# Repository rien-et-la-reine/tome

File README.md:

# tome

seeing if i can make a clamshell ereader + music player from scratch(-ish)

inspired in part by The Open Book (https://github.com/joeycastillo/The-Open-Book)

Firmware: [tavernkeep](https://github.com/rien-et-la-reine/tavernkeep)

## License

Copyright Harsh Patel 2026.

The following notice applies to all hardware design files in this repository.

This source describes Open Hardware and is licensed under the CERN-OHL-S v2.
You may redistribute and modify this source and make products using it under the terms of the CERN-OHL-S v2 (https://ohwr.org/cern_ohl_s_v2.txt).

This source is distributed WITHOUT ANY EXPRESS OR IMPLIED WARRANTY, INCLUDING OF MERCHANTABILITY, SATISFACTORY QUALITY AND FITNESS FOR A PARTICULAR PURPOSE.
Please see the CERN-OHL-S v2 for applicable conditions.

Source location: https://github.com/rien-et-la-reine/tome

As per CERN-OHL-S v2 section 4, should you produce hardware based on this source, you must where practicable maintain the Source Location visible on the external case or other products you make using this source.

Commits up to and including `8ce5c31` were published under CC BY-SA 4.0 and remain available under that licence.

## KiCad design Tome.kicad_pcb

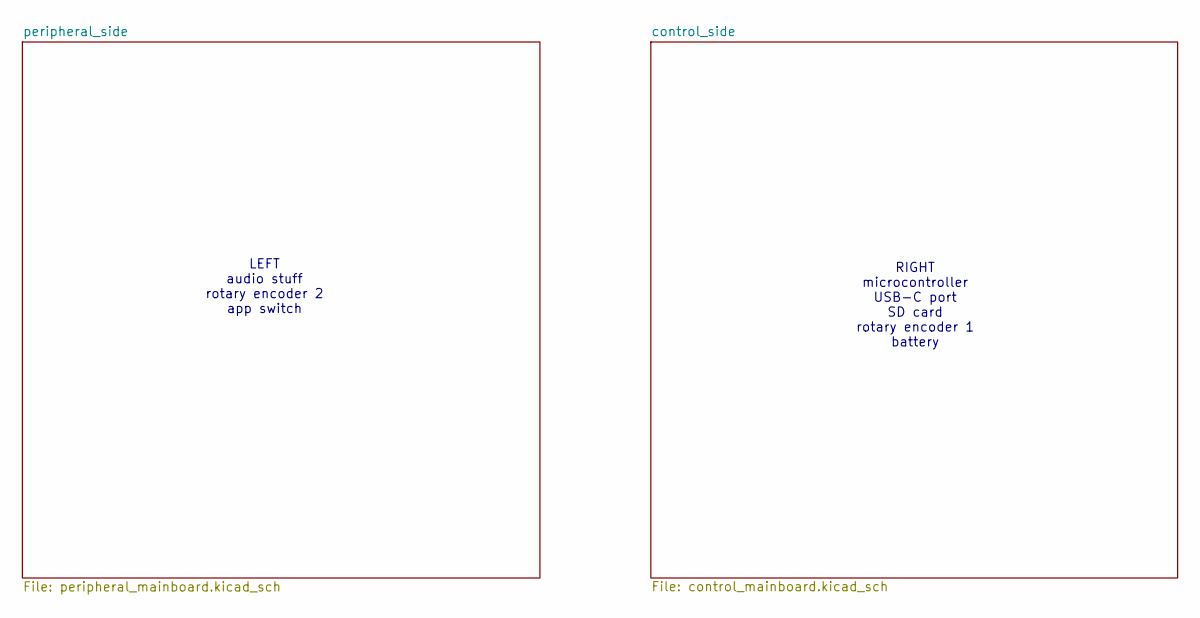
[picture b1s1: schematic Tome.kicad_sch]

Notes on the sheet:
RIGHT microcontroller USB-C port SD card rotary encoder 1 battery
LEFT audio stuff rotary encoder 2 app switch

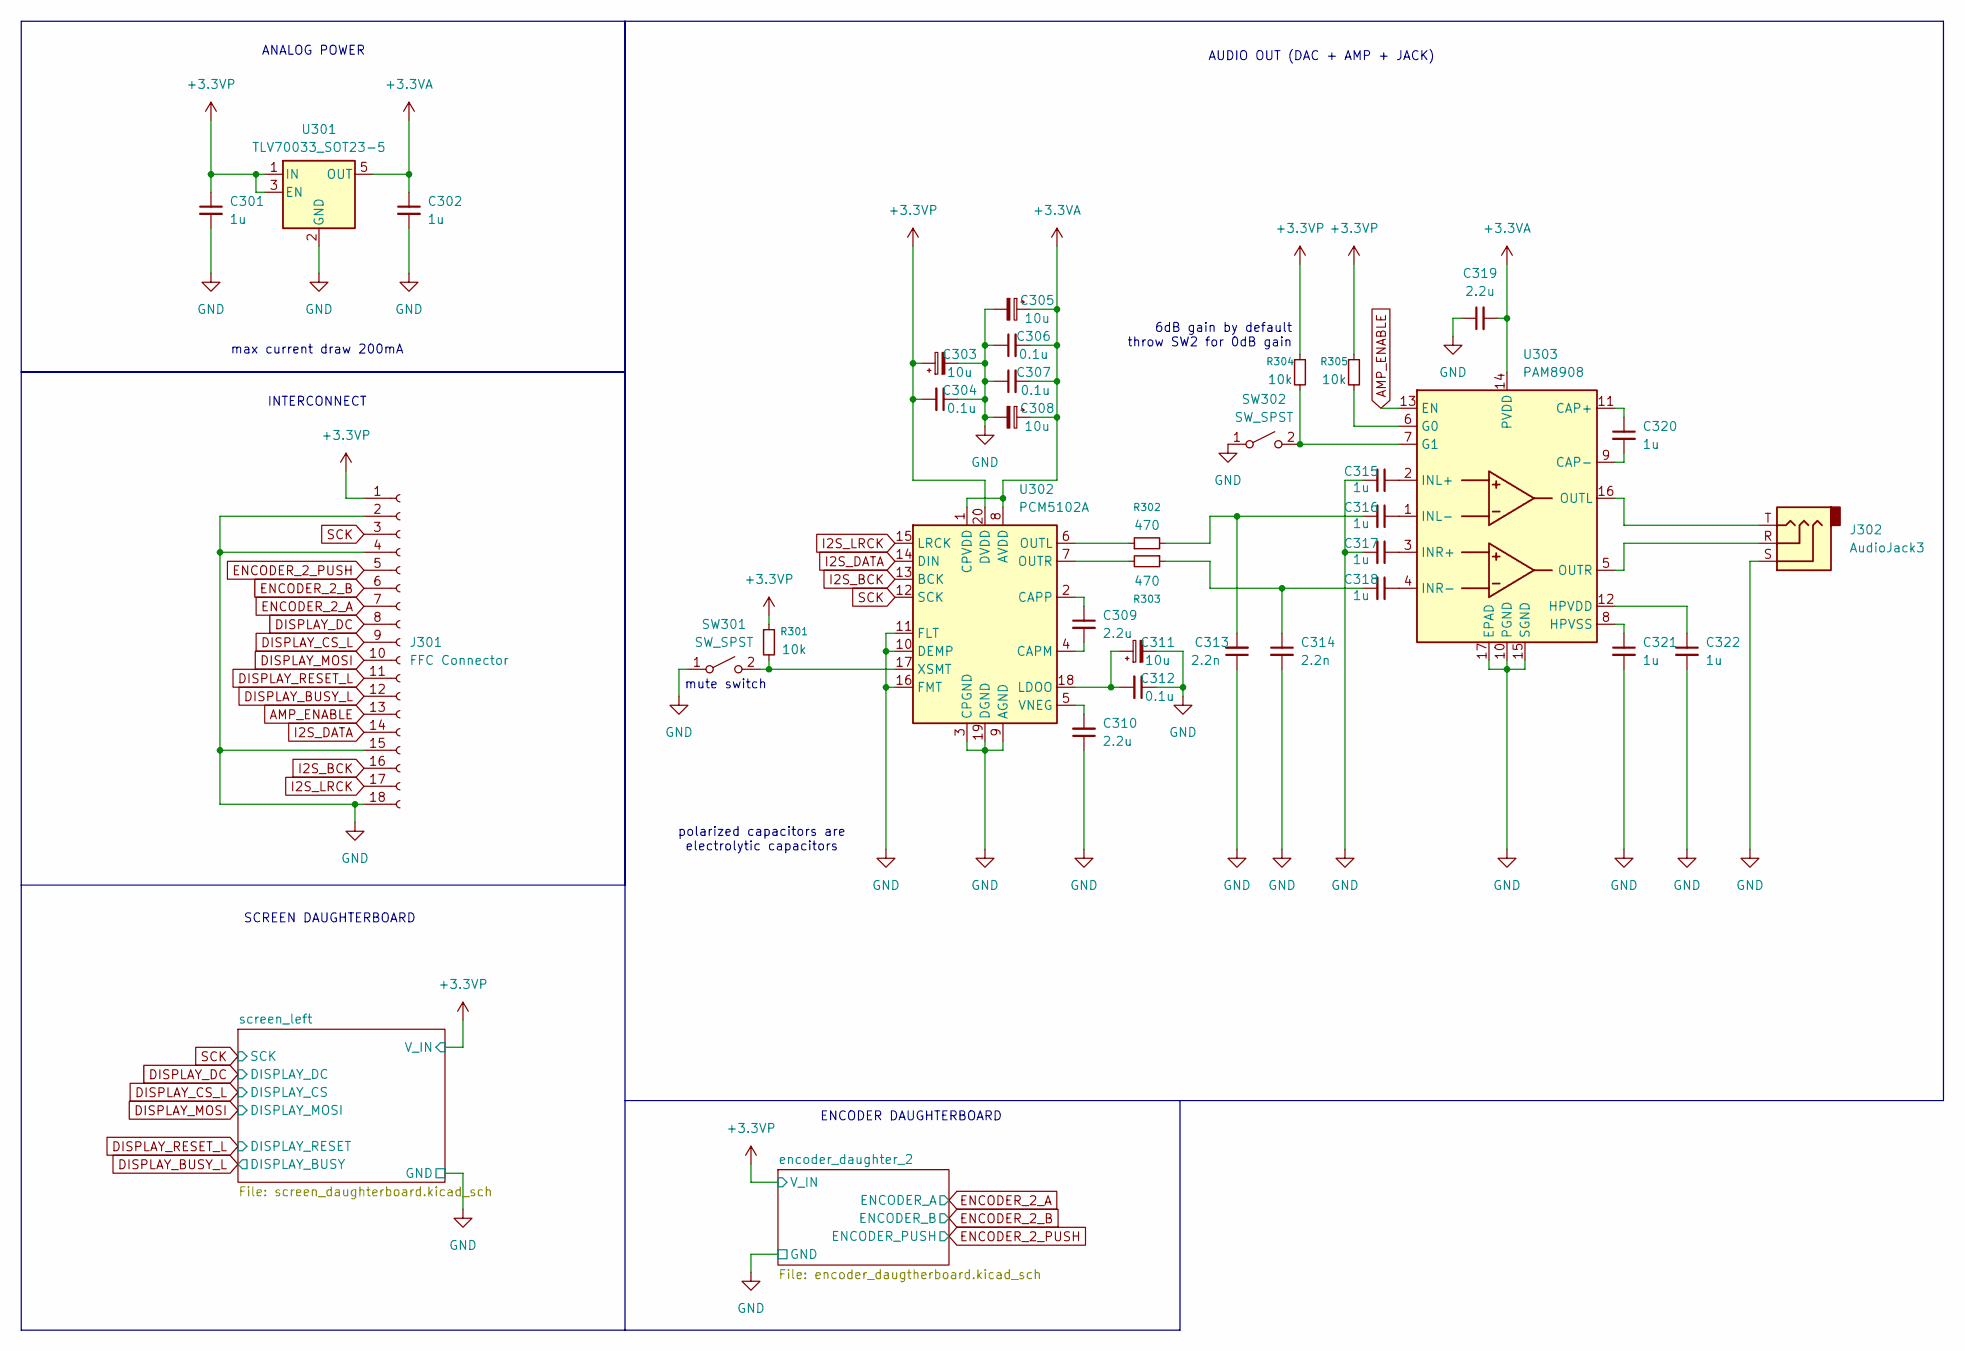
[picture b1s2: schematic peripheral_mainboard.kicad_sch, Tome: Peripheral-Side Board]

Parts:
C301, C302, C315, C316, C317, C318, C320, C321, C322: 1u; C_0805_2012Metric
C303, C305, C308, C311: 10u; CP_Elec_4x4.5
C304, C306, C307, C312: 0.1u; C_1206_3216Metric
C309, C310, C319: 2.2u; C_0402_1005Metric
C313, C314: 2.2n; C_0805_2012Metric
J301: FFC Connector; JUSHUO_AFA07-S18FCA-00_1x18-1MP_P1.0mm_Horizontal
J302: AudioJack3; Jack_3.5mm_CUI_SJ1-3523N_Horizontal
R301, R304, R305: 10k; R_1206_3216Metric
R302, R303: 470; R_0603_1608Metric
SW301, SW302: SW_SPST; SW_SPDT_CK_JS102011SAQN
U301: TLV70033_SOT23-5; SOT-23-5
U302: PCM5102A; TSSOP-20_4.4x6.5mm_P0.65mm
U303: PAM8908; QFN-16-1EP_3x3mm_P0.5mm_EP1.7x1.7mm

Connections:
+3.3VA: C302.1, C305.1, C306.2, C307.2, C308.1, C319.2, U301.5 (OUT), U302.1 (CPVDD), U302.8 (AVDD), U303.14 (PVDD)
+3.3VP: C301.1, C303.1, C304.2, J301.1, R301.1, R304.1, R305.1, U301.1 (IN), U301.3 (EN), U302.20 (DVDD); also elsewhere on the board
AMP_ENABLE: J301.13, U303.13 (EN); also elsewhere on the board
DISPLAY_BUSY_L: J301.12; also elsewhere on the board
DISPLAY_CS_L: J301.9; also elsewhere on the board
DISPLAY_DC: J301.8; also elsewhere on the board
DISPLAY_MOSI: J301.10; also elsewhere on the board
DISPLAY_RESET_L: J301.11; also elsewhere on the board
ENCODER_2_A: J301.7; also elsewhere on the board
ENCODER_2_B: J301.6; also elsewhere on the board
ENCODER_2_PUSH: J301.5; also elsewhere on the board
GND: C301.2, C302.2, C303.2, C304.1, C305.2, C306.1, C307.1, C308.2, C310.1, C311.2, C312.1, C313.1, C314.2, C315.2, C317.2, C319.1, C321.2, C322.2, J301.2, J301.4, J301.15, J301.18, J302.S, SW301.1 (A), SW302.1 (A), U301.2 (GND), U302.3 (CPGND), U302.9 (AGND), U302.10 (DEMP), U302.11 (FLT), U302.16 (FMT), U302.19 (DGND), U303.10 (PGND), U303.15 (SGND), U303.17 (EPAD); also elsewhere on the board
I2S_BCK: J301.16, U302.13 (BCK); also elsewhere on the board
I2S_DATA: J301.14, U302.14 (DIN); also elsewhere on the board
I2S_LRCK: J301.17, U302.15 (LRCK); also elsewhere on the board
unnamed: C313.2, C316.2, R302.2
unnamed: C314.1, C318.2, R303.1
unnamed: R301.2, SW301.2 (B), U302.17 (XSMT)
unnamed: R304.2, SW302.2 (B), U303.7 (G1)
unnamed: C309.2, U302.4 (CAPM)
unnamed: C309.1, U302.2 (CAPP)
unnamed: C311.1, C312.2, U302.18 (LDOO)
unnamed: R302.1, U302.6 (OUTL)
unnamed: R303.2, U302.7 (OUTR)
unnamed: C310.2, U302.5 (VNEG)
unnamed: C320.1, U303.11 (CAP+)
unnamed: C320.2, U303.9 (CAP-)
unnamed: R305.2, U303.6 (G0)
unnamed: C322.1, U303.12 (HPVDD)
unnamed: C321.1, U303.8 (HPVSS)
unnamed: C315.1, U303.2 (INL+)
unnamed: C316.1, U303.1 (INL-)
unnamed: C317.1, U303.3 (INR+)
unnamed: C318.1, U303.4 (INR-)
unnamed: J302.T, U303.16 (OUTL)
unnamed: J302.R, U303.5 (OUTR)
SCK: J301.3, U302.12 (SCK); also elsewhere on the board

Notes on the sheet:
6dB gain by default throw SW2 for 0dB gain
SCREEN DAUGHTERBOARD
polarized capacitors are electrolytic capacitors
max current draw 200mA
ANALOG POWER
AUDIO OUT (DAC + AMP + JACK)
INTERCONNECT
ENCODER DAUGHTERBOARD
mute switch

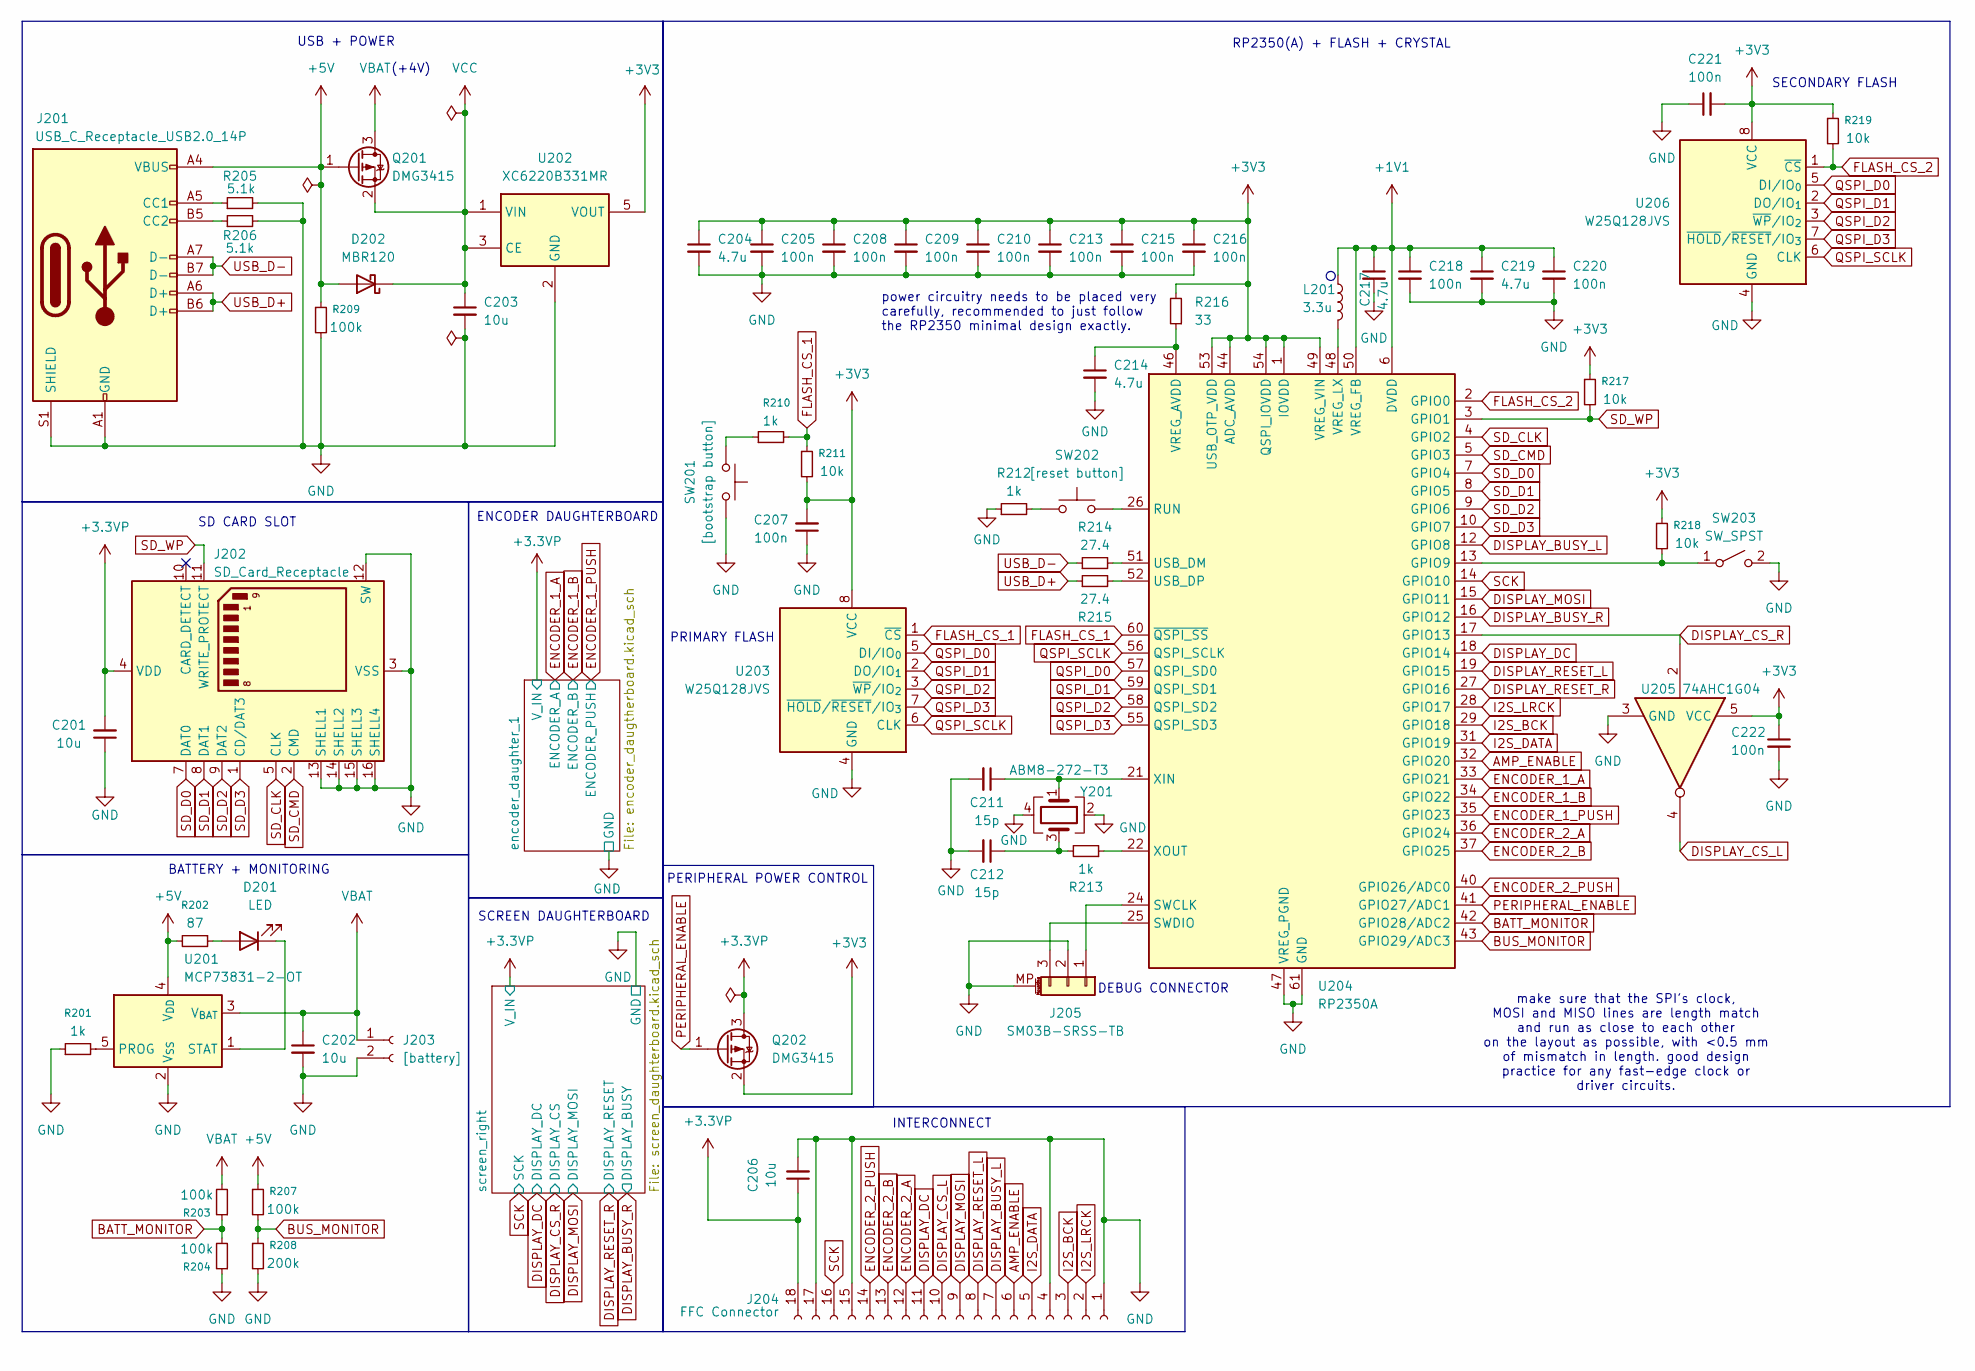
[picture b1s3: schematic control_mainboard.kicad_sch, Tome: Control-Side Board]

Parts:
C201, C202, C206: 10u; C_0805_2012Metric
C203: 10u; C_0402_1005Metric
C204, C214, C217, C219: 4.7u; C_0402_1005Metric
C205, C207, C208, C209, C210, C213, C215, C216, C218, C220, C221, C222: 100n; C_0402_1005Metric
C211, C212: 15p; C_0402_1005Metric
D201: LED; LED_0603_1608Metric
D202: MBR120; D_SOD-123
J201: USB_C_Receptacle_USB2.0_14P; USB_C_Receptacle_GCT_USB4105-xx-A_16P_TopMnt_Horizontal
J202: SD_Card_Receptacle; SD_Hirose_DM1AA_SF_PEJ82
J203: [battery]; JST_PH_S2B-PH-K_1x02_P2.00mm_Horizontal
J204: FFC Connector; JUSHUO_AFA07-S18FCA-00_1x18-1MP_P1.0mm_Horizontal
J205: SM03B-SRSS-TB; JST_SH_SM03B-SRSS-TB_1x03-1MP_P1.00mm_Horizontal
L201: 3.3u; L_pol_2016
Q201, Q202: DMG3415; SOT-23
R201: 1k; R_1206_3216Metric
R202: 87; R_1206_3216Metric
R203, R204, R207: 100k; R_1206_3216Metric
R205, R206: 5.1k; R_0402_1005Metric
R208: 200k; R_0805_2012Metric
R209: 100k; R_0402_1005Metric
R210, R213: 1k; R_0402_1005Metric
R211, R219: 10k; R_0402_1005Metric
R212: 1k; R_0603_1608Metric
R214, R215: 27.4; R_0402_1005Metric
R216: 33; R_0402_1005Metric
R217, R218: 10k; R_1206_3216Metric
SW201: [bootstrap button]; Panasonic_EVQPUK_EVQPUB
SW202: [reset button]; Panasonic_EVQPUK_EVQPUB
SW203: SW_SPST; SW_SPDT_CK_JS102011SAQN
U201: MCP73831-2-OT; SOT-23-5
U202: XC6220B331MR; SOT-23-5
U203, U206: W25Q128JVS; SOIC-8_5.3x5.3mm_P1.27mm
U204: RP2350A; QFN-60-1EP_7x7mm_P0.4mm_EP3.4x3.4mm
U205: 74AHC1G04; SOT-23-5_HandSoldering
Y201: ABM8-272-T3; Crystal_SMD_3225-4Pin_3.2x2.5mm

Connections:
+1V1: C217.1, C218.1, C219.1, C220.1, L201.1, U204.6 (DVDD), U204.23 (DVDD), U204.39 (DVDD), U204.50 (VREG_FB)
+3.3VP: C201.2, C206.1, J202.4 (VDD), J204.18, Q202.3 (D); also elsewhere on the board
+3V3: C204.1, C205.1, C207.2, C208.1, C209.1, C210.1, C213.1, C215.1, C216.1, C221.2, C222.1, Q202.2 (S), R211.2, R216.2, R217.1, R218.1, R219.1, U202.5 (VOUT), U203.8 (VCC), U204.1 (IOVDD), U204.11 (IOVDD), U204.20 (IOVDD), U204.30 (IOVDD), U204.38 (IOVDD), U204.44 (ADC_AVDD), U204.45 (IOVDD), U204.49 (VREG_VIN), U204.53 (USB_OTP_VDD), U204.54 (QSPI_IOVDD), U205.5 (VCC), U206.8 (VCC)
+5V: D202.2 (A), J201.A4 (VBUS), J201.A9 (VBUS), J201.B4 (VBUS), J201.B9 (VBUS), Q201.1 (G), R202.2, R207.1, R209.1, U201.4 (V_{DD})
AMP_ENABLE: J204.6, U204.32 (GPIO20); also elsewhere on the board
BATT_MONITOR: R203.1, R204.2, U204.42 (GPIO28/ADC2)
BUS_MONITOR: R207.2, R208.1, U204.43 (GPIO29/ADC3)
DISPLAY_BUSY_L: J204.7, U204.12 (GPIO8); also elsewhere on the board
DISPLAY_BUSY_R: U204.16 (GPIO12); also elsewhere on the board
DISPLAY_CS_L: J204.10, U205.4; also elsewhere on the board
DISPLAY_CS_R: U204.17 (GPIO13), U205.2; also elsewhere on the board
DISPLAY_DC: J204.11, U204.18 (GPIO14); also elsewhere on the board
DISPLAY_MOSI: J204.9, U204.15 (GPIO11); also elsewhere on the board
DISPLAY_RESET_L: J204.8, U204.19 (GPIO15); also elsewhere on the board
DISPLAY_RESET_R: U204.27 (GPIO16); also elsewhere on the board
ENCODER_1_A: U204.33 (GPIO21); also elsewhere on the board
ENCODER_1_B: U204.34 (GPIO22); also elsewhere on the board
ENCODER_1_PUSH: U204.35 (GPIO23); also elsewhere on the board
ENCODER_2_A: J204.12, U204.36 (GPIO24); also elsewhere on the board
ENCODER_2_B: J204.13, U204.37 (GPIO25); also elsewhere on the board
ENCODER_2_PUSH: J204.14, U204.40 (GPIO26/ADC0); also elsewhere on the board
FLASH_CS_1: R210.2, R211.1, U203.1 (~CS), U204.60 (~QSPI_SS)
FLASH_CS_2: R219.2, U204.2 (GPIO0), U206.1 (~CS)
GND: C201.1, C202.2, C203.2, C204.2, C205.2, C206.2, C207.1, C208.2, C209.2, C210.2, C211.2, C212.2, C213.2, C214.2, C215.2, C216.2, C217.2, C218.2, C219.2, C220.2, C221.1, C222.2, J201.A1 (GND), J201.A12 (GND), J201.B1 (GND), J201.B12 (GND), J201.S1 (SHIELD), J202.3 (VSS), J202.6 (VSS), J202.12 (SW), J202.13 (SHELL1), J202.14 (SHELL2), J202.15 (SHELL3), J202.16 (SHELL4), J203.2, J204.1, J204.4, J204.15, J204.17, J205.2, J205.MP (MountPin), R201.1, R204.1, R205.2, R206.2, R208.2, R209.2, R212.1, SW201.2, SW203.2 (B), U201.2 (V_{SS}), U202.2 (GND), U203.4 (GND), U204.47 (VREG_PGND), U204.61 (GND), U205.3 (GND), U206.4 (GND), Y201.2, Y201.4; also elsewhere on the board
I2S_BCK: J204.3, U204.29 (GPIO18); also elsewhere on the board
I2S_DATA: J204.5, U204.31 (GPIO19); also elsewhere on the board
I2S_LRCK: J204.2, U204.28 (GPIO17); also elsewhere on the board
unnamed: C212.1, R213.2, Y201.3
unnamed: D201.2 (A), R202.1
unnamed: D201.1 (K), U201.1 (STAT)
unnamed: J201.A5 (CC1), R205.1
unnamed: J201.B5 (CC2), R206.1
unnamed: J205.1, U204.24 (SWCLK)
unnamed: J205.3, U204.25 (SWDIO)
unnamed: R210.1, SW201.1
unnamed: R212.2, SW202.1
unnamed: R218.2, SW203.1 (A), U204.13 (GPIO9)
unnamed: R201.2, U201.5 (PROG)
unnamed: SW202.2, U204.26 (RUN)
unnamed: R214.2, U204.51 (USB_DM)
unnamed: R215.2, U204.52 (USB_DP)
unnamed: C214.1, R216.1, U204.46 (VREG_AVDD)
unnamed: L201.2, U204.48 (VREG_LX)
unnamed: C211.1, U204.21 (XIN), Y201.1
unnamed: R213.1, U204.22 (XOUT)
PERIPHERAL_ENABLE: Q202.1 (G), U204.41 (GPIO27/ADC1)
QSPI_D0: U203.5 (DI/IO_{0}), U204.57 (QSPI_SD0), U206.5 (DI/IO_{0})
QSPI_D1: U203.2 (DO/IO_{1}), U204.59 (QSPI_SD1), U206.2 (DO/IO_{1})
QSPI_D2: U203.3 (~WP/IO_{2}), U204.58 (QSPI_SD2), U206.3 (~WP/IO_{2})
QSPI_D3: U203.7 (~HOLD/~RESET/IO_{3}), U204.55 (QSPI_SD3), U206.7 (~HOLD/~RESET/IO_{3})
QSPI_SCLK: U203.6 (CLK), U204.56 (QSPI_SCLK), U206.6 (CLK)
SCK: J204.16, U204.14 (GPIO10); also elsewhere on the board
SD_CLK: J202.5 (CLK), U204.4 (GPIO2)
SD_CMD: J202.2 (CMD), U204.5 (GPIO3)
SD_D0: J202.7 (DAT0), U204.7 (GPIO4)
SD_D1: J202.8 (DAT1), U204.8 (GPIO5)
SD_D2: J202.9 (DAT2), U204.9 (GPIO6)
SD_D3: J202.1 (CD/DAT3), U204.10 (GPIO7)
SD_WP: J202.11 (WRITE_PROTECT), R217.2, U204.3 (GPIO1)
USB_D+: J201.A6 (D+), J201.B6 (D+), R215.1
USB_D-: J201.A7 (D-), J201.B7 (D-), R214.1
VBAT: C202.1, J203.1, Q201.3 (D), R203.2, U201.3 (V_{BAT})
VCC: C203.1, D202.1 (K), Q201.2 (S), U202.1 (VIN), U202.3 (CE)

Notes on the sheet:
SCREEN DAUGHTERBOARD
SECONDARY FLASH
DEBUG CONNECTOR
SD CARD SLOT
make sure that the SPI's clock, MOSI and MISO lines are length match and run as close to each other on the layout as possible, with <0.5 mm of mismatch in length. good design practice for any fast-edge clock or driver circuits.
INTERCONNECT
power circuitry needs to be placed very carefully, recommended to just follow the RP2350 minimal design exactly.
BATTERY + MONITORING
PRIMARY FLASH
ENCODER DAUGHTERBOARD
(+4V)
PERIPHERAL POWER CONTROL
USB + POWER
RP2350(A) + FLASH + CRYSTAL

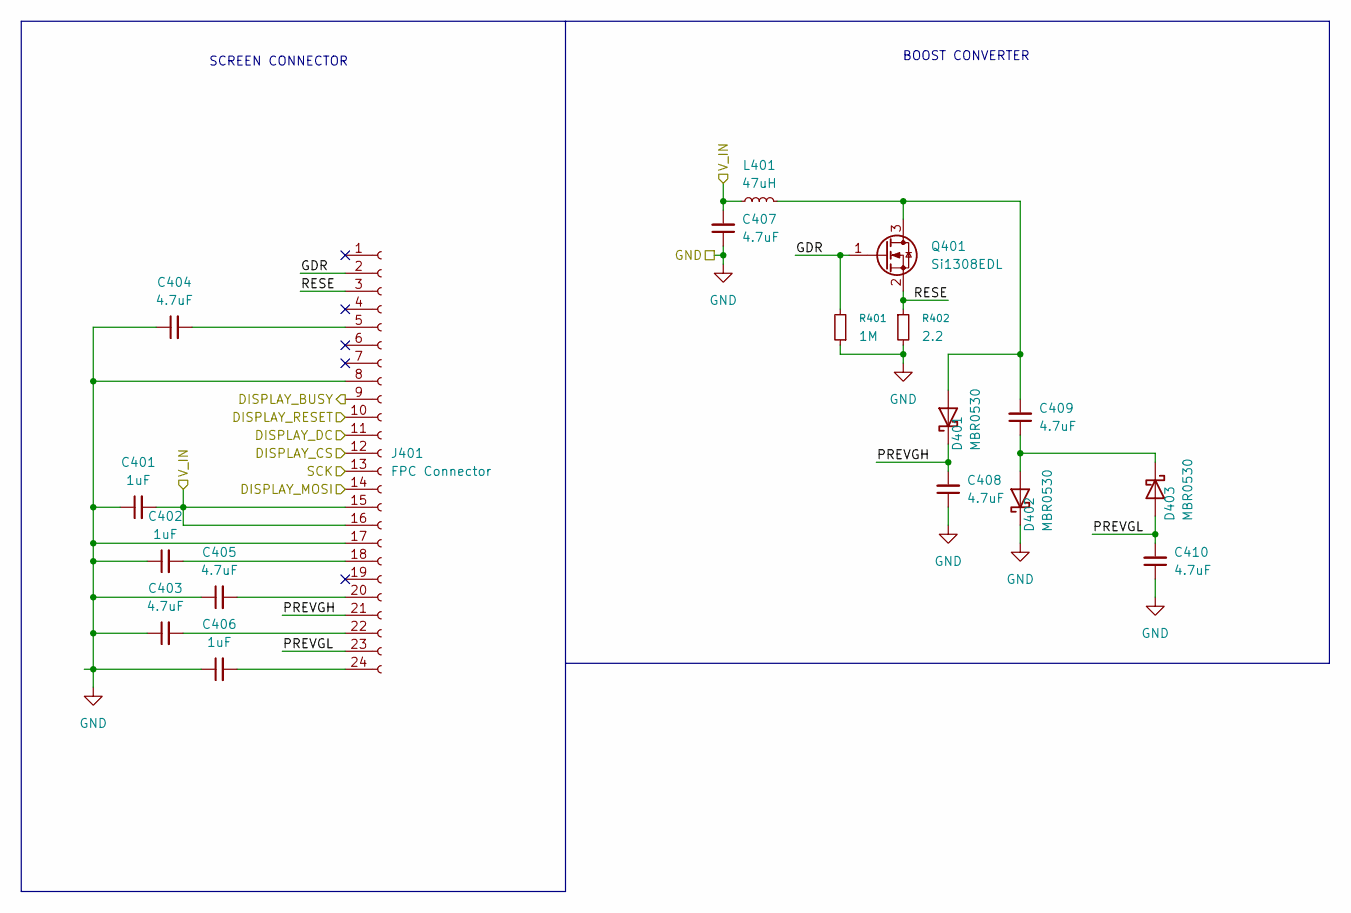
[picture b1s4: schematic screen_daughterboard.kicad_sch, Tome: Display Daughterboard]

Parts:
C401, C402, C406: 1uF; C_0805_2012Metric
C403, C404, C405, C407, C408, C409, C410: 4.7uF; C_0402_1005Metric
D401, D402, D403: MBR0530; D_SOD-123
J401: FPC Connector; Hirose_FH12-24S-0.5SH_1x24-1MP_P0.50mm_Horizontal
L401: 47uH; L_APV_ANR3015
Q401: Si1308EDL; SOT-323_SC-70
R401: 1M; R_0805_2012Metric
R402: 2.2; R_0603_1608Metric

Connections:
+3.3VP: C401.2, C407.2, J401.15, J401.16, L401.1; also elsewhere on the board
/control_side/screen_right/GDR: J401.2, Q401.1 (G), R401.2
/control_side/screen_right/PREVGH: C408.2, D401.1 (K), J401.21
/control_side/screen_right/PREVGL: C410.2, D403.2 (A), J401.23
/control_side/screen_right/RESE: J401.3, Q401.2 (S), R402.1
DISPLAY_BUSY_R: J401.9; also elsewhere on the board
DISPLAY_CS_R: J401.12; also elsewhere on the board
DISPLAY_DC: J401.11; also elsewhere on the board
DISPLAY_MOSI: J401.14; also elsewhere on the board
DISPLAY_RESET_R: J401.10; also elsewhere on the board
GND: C401.1, C402.1, C403.1, C404.1, C405.1, C406.1, C407.1, C408.1, C410.1, D402.1 (K), J401.8, J401.17, R401.1, R402.2; also elsewhere on the board
unnamed: C409.2, D401.2 (A), L401.2, Q401.3 (D)
unnamed: C409.1, D402.2 (A), D403.1 (K)
unnamed: C404.2, J401.5
unnamed: C402.2, J401.18
unnamed: C405.2, J401.20
unnamed: C403.2, J401.22
unnamed: C406.2, J401.24
SCK: J401.13; also elsewhere on the board

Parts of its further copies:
C501, C502, C506: 1uF; C_0805_2012Metric
C503, C504, C505, C507, C508, C509, C510: 4.7uF; C_0402_1005Metric
D501, D502, D503: MBR0530; D_SOD-123
J501: FPC Connector; Hirose_FH12-24S-0.5SH_1x24-1MP_P0.50mm_Horizontal
L501: 47uH; L_APV_ANR3015
Q501: Si1308EDL; SOT-323_SC-70
R501: 1M; R_0805_2012Metric
R502: 2.2; R_0603_1608Metric

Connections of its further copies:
+3.3VP: C501.2, C507.2, J501.15, J501.16, L501.1; also elsewhere on the board
/peripheral_side/screen_left/GDR: J501.2, Q501.1 (G), R501.2
/peripheral_side/screen_left/PREVGH: C508.2, D501.1 (K), J501.21
/peripheral_side/screen_left/PREVGL: C510.2, D503.2 (A), J501.23
/peripheral_side/screen_left/RESE: J501.3, Q501.2 (S), R502.1
DISPLAY_BUSY_L: J501.9; also elsewhere on the board
DISPLAY_CS_L: J501.12; also elsewhere on the board
DISPLAY_DC: J501.11; also elsewhere on the board
DISPLAY_MOSI: J501.14; also elsewhere on the board
DISPLAY_RESET_L: J501.10; also elsewhere on the board
GND: C501.1, C502.1, C503.1, C504.1, C505.1, C506.1, C507.1, C508.1, C510.1, D502.1 (K), J501.8, J501.17, R501.1, R502.2; also elsewhere on the board
unnamed: C509.2, D501.2 (A), L501.2, Q501.3 (D)
unnamed: C509.1, D502.2 (A), D503.1 (K)
unnamed: C504.2, J501.5
unnamed: C502.2, J501.18
unnamed: C505.2, J501.20
unnamed: C503.2, J501.22
unnamed: C506.2, J501.24
SCK: J501.13; also elsewhere on the board

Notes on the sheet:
BOOST CONVERTER
SCREEN CONNECTOR

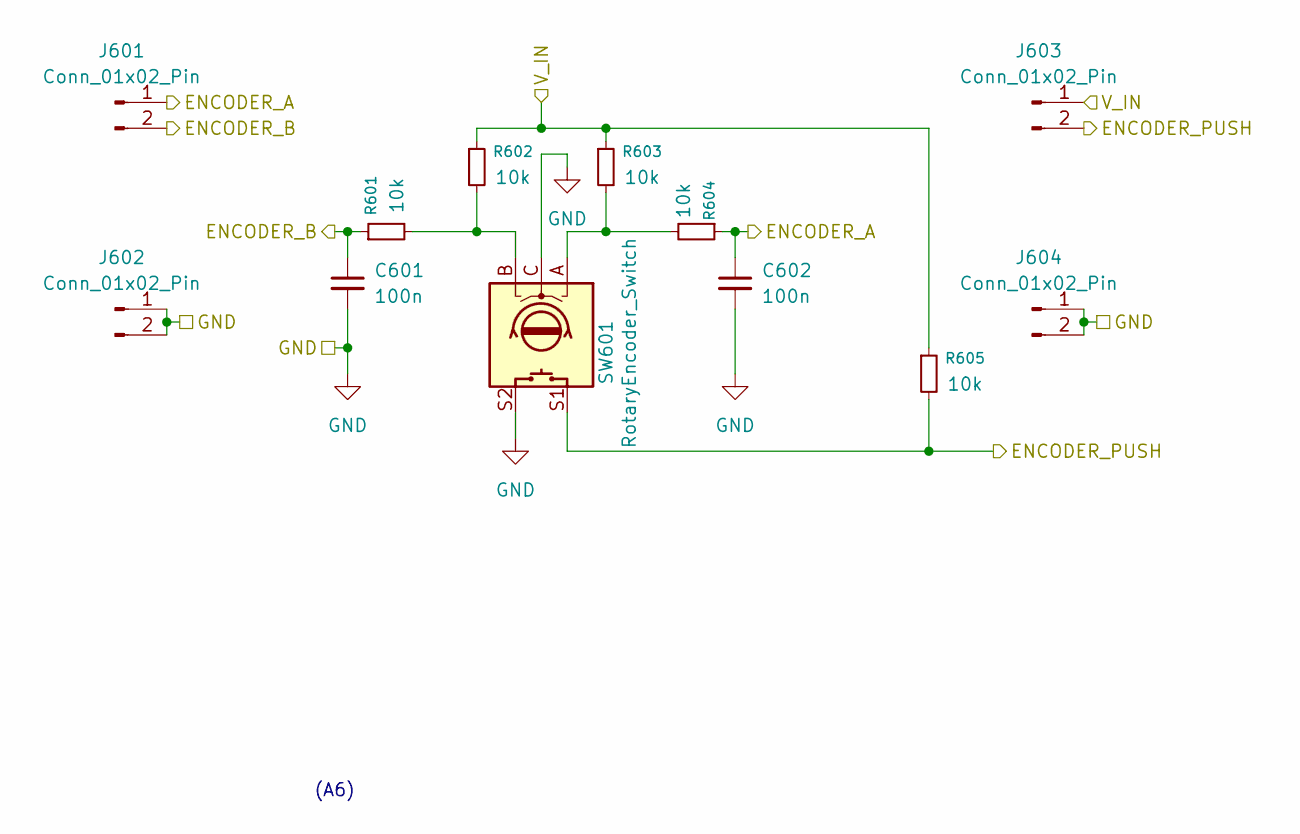
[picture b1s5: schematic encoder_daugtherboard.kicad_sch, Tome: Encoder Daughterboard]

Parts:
C601, C602: 100n; C_0402_1005Metric
J601, J602, J603, J604: Conn_01x02_Pin; PinHeader_1x02_P2.00mm_Vertical
R601, R602, R603, R604, R605: 10k; R_1206_3216Metric
SW601: RotaryEncoder_Switch; RotaryEncoder_Alps_EC11E-Switch_Vertical_H20mm

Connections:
+3.3VP: J603.1, R602.1, R603.1, R605.1; also elsewhere on the board
ENCODER_1_A: C602.1, J601.1, R604.1; also elsewhere on the board
ENCODER_1_B: C601.1, J601.2, R601.1; also elsewhere on the board
ENCODER_1_PUSH: J603.2, R605.2, SW601.S1; also elsewhere on the board
GND: C601.2, C602.2, J602.1, J602.2, J604.1, J604.2, SW601.C, SW601.S2; also elsewhere on the board
unnamed: R601.2, R602.2, SW601.B
unnamed: R603.2, R604.2, SW601.A

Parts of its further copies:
C701, C702: 100n; C_0402_1005Metric
J701, J702, J703, J704: Conn_01x02_Pin; PinHeader_1x02_P2.00mm_Vertical
R701, R702, R703, R704, R705: 10k; R_1206_3216Metric
SW701: RotaryEncoder_Switch; RotaryEncoder_Alps_EC11E-Switch_Vertical_H20mm

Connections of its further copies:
+3.3VP: J703.1, R702.1, R703.1, R705.1; also elsewhere on the board
ENCODER_2_A: C702.1, J701.1, R704.1; also elsewhere on the board
ENCODER_2_B: C701.1, J701.2, R701.1; also elsewhere on the board
ENCODER_2_PUSH: J703.2, R705.2, SW701.S1; also elsewhere on the board
GND: C701.2, C702.2, J702.1, J702.2, J704.1, J704.2, SW701.C, SW701.S2; also elsewhere on the board
unnamed: R701.2, R702.2, SW701.B
unnamed: R703.2, R704.2, SW701.A

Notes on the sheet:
(A6)

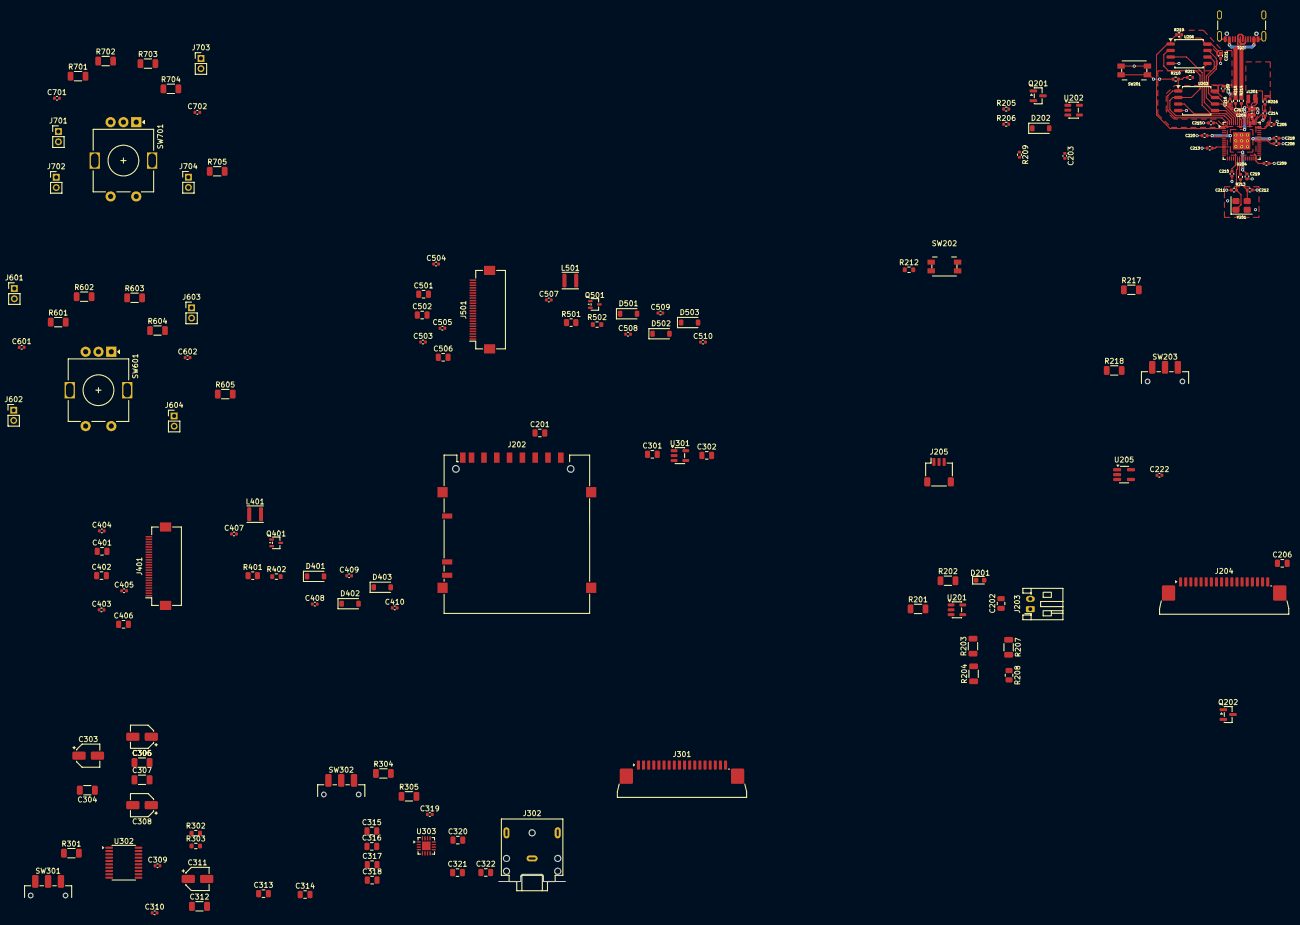
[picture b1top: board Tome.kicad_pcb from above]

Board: 2 copper layers, 155 parts (0 on the bottom side), 111 nets.

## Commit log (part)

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2026-02-05 upload KiCad Project
2026-02-05 update page size
2026-02-05 Create LICENSE
2026-02-05 unused schematic removal
2026-02-05 adjusting pin assignments
2026-02-05 fixing pullup resistors
2026-02-06 removing incorrect pullups
2026-02-06 split schematic based on physical PCB split
2026-02-06 fixed page numbers
    and adjusted some label types
2026-02-07 separating schematics based on board
    finished splitting every component up into separate sheets in the schematic based on what physical board it's going on
2026-02-08 assigning pcb footprints
    assigned pcb footprints to most components:
    - rotary encoder footprint will need slight modification to fit bourns PEC11L
    - need to finalize components for reset button and the four switches before assigning those footprints
2026-02-08 removed external footprint/model
    these were from ultralibrarian and should never have been included here, my bad
2026-02-08 replaced DAC footprint
    there was literally a built-in footprint for the DAC in kicad already the whole time...
2026-02-09 finalizing schematics
    connected the new DAC footprint, filled in title blocks
2026-02-11 corrected connector orientation
2026-02-12 working on PCBs
2026-02-12 assigned switch and reset button footprints
    all footprints now assigned*
    *will probably need something to connect the encoder daughterboard to the main boards
2026-02-12 different encoder board layout
2026-02-16 workshopping encoder board
2026-02-16 cleanup
2026-02-19 Update fp-info-cache
2026-02-20 switching to RP2350
2026-02-23 wiring write protect to card detect
    need to reduce GPIO pins used so wiring write protect on the SD card port to lock card detect high directly instead of connecting to the microcontroller. this should prevent the card from being detec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
2026-02-23 simplified card detect/write protect
    read the datasheet wrong, can just use the write protect pin, it's open when inserted card is write protected and also when there is no card, and pulled down when a card that is write enabled is inse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
2026-02-23 update left/right interconnect
2026-02-23 charge status LED
2026-02-24 updating schematic
2026-02-24 added secondary flash to schematic
